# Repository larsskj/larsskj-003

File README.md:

A simple board for connecting LEDs
==================================

### larsskj-003

This project is a simple board to connect LEDs - or virtually anything - to a flatcable. It's intended to be used with my other boards for model railway structures.

For more information, visit the [project homepage](https://larsskj.org/projects/larsskj-003).

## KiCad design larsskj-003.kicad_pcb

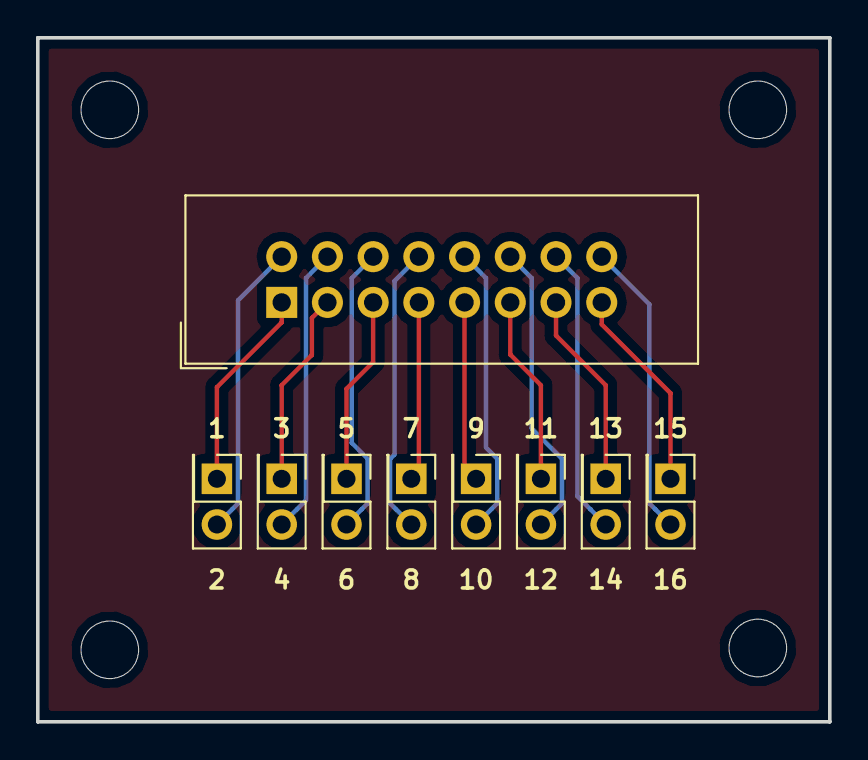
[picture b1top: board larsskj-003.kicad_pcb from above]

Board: 2 copper layers, 44.0 x 38.0 mm, 9 parts (0 on the bottom side), 16 nets.

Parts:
J1: IDC connector; IDC-Header_2x08_P2.54mm_Vertical
J2, J3, J4, J5, J6, J7, J8, J9: Conn_02x01; PinHeader_2x01_P2.54mm_Vertical

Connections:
unnamed: J1.1, J2.1
unnamed: J1.2, J2.2
unnamed: J1.3, J3.1
unnamed: J1.4, J3.2
unnamed: J1.5, J4.1
unnamed: J1.6, J4.2
unnamed: J1.7, J5.1
unnamed: J1.8, J5.2
unnamed: J1.9, J6.1
unnamed: J1.10, J6.2
unnamed: J1.11, J7.1
unnamed: J1.12, J7.2
unnamed: J1.13, J8.1
unnamed: J1.14, J8.2
unnamed: J1.15, J9.1
unnamed: J1.16, J9.2

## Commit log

2019-04-12 README.md added
2019-04-15 Improved PCB layout
2019-04-15 3D graphic added.
